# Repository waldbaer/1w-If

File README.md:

# 

An ESP32-based 1-Wire interface supporting access with physical ethernet and MQTT protocol.

**Overview**

**Hardware**

[Schematic](doc/hardware/1w-If_schematic.pdf)

## Key Features

* Access 1-wire devices via ethernet / MQTT protocol
* 4 independent 1-Wire channels with hardware bus masters
* Over-the-air (OTA) updates (web interface and espota protocol)
* Responsive web interface for configuration
  <br/>
  
* NTP for clock synchronization
* 3D printed housing

## Supported 1-Wire devices

* DS2401 / DS2411 (Silicon Serial Number)
  * Unique Unique 64-Bit Serial Code

* DS18B20 (Temperature sensor)
  * Configurable resolution temperature

* DS2438  (Smart Battery Monitor)
  * Temperature, VAD, VDD

## Web-Interface

Default login:
- Username: `admin`
- Password: `1w-If`

## MQTT API
`%topic%` is a configurable prefix. Default: `1wIf`

### Commands

General MQTT topic for commands: `%topic%/cmd`

General MQTT topic for responses and status: `%topic%/stat`

Payload Format:

```
{
  "action": "<command>",
  ... action specific parameters / attributes ...
}
```

#### Command 'Restart'

Restart the entire system.
```
{
  "action": "restart",
}
```

Response:
```
{
  "action": "restart",
  "acknowledge": true,
  "time": "2026-02-03 20:20:07.955"
}
```

#### Command 'SysInfo'

Get system info.
```
{
  "action": "sysinfo",
}
```

Response:
```
{
  "action": "sysinfo",
  "state": "online",
  "version": "1.1.0",
  "uptime": "14d 12:07:12.834",
  "board_temp": 43.9,
  "ethernet": {
    "ip": "192.168.0.100",
    "mac": "89:30:5A:47:7D:0C",
    "link_speed": 100,
    "link_mode": "FULL_DUPLEX"
  },
  "time": "2026-03-15 17:02:09.720"
}
```

#### Command 'Scan'

Scan 1-wire buses for all available devices:

```
{
  "action": "scan",
}
```

Scan 1-wire buses for availability of a specific device:

```
{
  "action": "scan",
  "device_id": "01.D2C79A1A0000"
}
```

Scan 1-wire buses for availability of a specific device family:

```
{
  "action": "scan",
  "family_code": 40
}
```

The response lists all available devices and the supported attributes (for `Read` / `Subscribe` / `Unsubscribe` commands):

Example Response:
```
{
  "action": "scan",
  "devices": [
    {
      "channel": 1,
      "device_id": "01.D2C79A1A0000",
      "presence": true,
      "attributes": ["presence"]
    },
    {
      "channel": 1,
      "device_id": "28.8F0945161301",
      "presence": true,
      "attributes": ["presence", "temperature"]
    },
    {
      "channel": 2,
      "device_id": "26.563743020000",
      "presence": true,
      "attributes": ["presence", "temperature", "VAD", "VDD"]
    },
    ...
  ],
  "time": "2026-02-03 20:16:46.010"
}
```

#### Command 'Read'

Read value(s) of a single 1-wire device:

```
{
  "action": "read",
  "device_id": "28.8F0945161301",
  "attribute": "temperature"
}
```

Example Response:
```
{
  "action": "read",
  "device": {
    "channel": 1,
    "device_id": "28.8F0945161301",
    "temperature": 24.75
  },
  "time": "2025-02-03 19:10:07.955"
}
```

Read value(s) of a specific device family:

```
{
  "action": "read",
  "family_code": 40,
  "attribute": "temperature"
}
```

Example Response:
```
{
  "action": "read",
  "family_code": 40,
  "devices": [
    {
      "channel": 1,
      "device_id": "28.8F0945161301",
      "temperature": 24.75
    },
    ...
  ],
  "time": "2025-02-03 18:10:02.844"
}
```

Also the presence of a device can be accessed via the read command using the attribute `presence`.
This is similar to the scan command.

```
{
  "action": "read",
  "device_id": "28.8F0945161301",
  "attribute": "presence"
}
```

Example Response:
```
{
  "action": "read",
  "device": {
    "channel": 2,
    "device_id": "28.8F0945161301",
    "presence": true
  },
  "time": "2026-01-17 05:19:02.170"
}
```

#### Command 'Subscribe / Unsubscribe'

Subscribe to cyclic updates for 1-wire device attributes.
After successful subscription this triggers internally a `Read` command with the configured internal time.

Unit of 'interval': _milliseconds_

```
{
  "action": "subscribe",
  "device_id": "28.8F0945161301",
  "attribute": "temperature",
  "interval": 1000
}
```

Example response acknowledging the successful subscription:
```
{
  "action": "subscribe",
  "acknowledge": true,
  "device": {
    "device_id": "28.8F0945161301"
  },
  "time": "2025-08-05 13:10:22.970"
}
```

Unsubscribe from the attribute:
```
{
  "action": "unsubscribe",
  "device_id": "28.8F0945161301",
  "attribute": "temperature"
}
```

It is also possible to subscribe to the attribute `presence` to get cyclic updates about the availability of dedicated
devices:
```
{
    "action": "subscribe",
    "device_id": "01.D2C79A1A0000",
    "attribute": "presence",
    "interval": 2000
}
```

Example of the `Read` command for attribute `presence` cyclically triggered by the subscription:
```
{
  "action": "read",
  "device": {
     "channel": 3,
     "device_id": "01.D2C79A1A0000",
     "presence": false
  },
  "time": "2026-01-20 14:55:36.781"
}
```

### Last Will and Testament

The MQTT Last Will and Testament (LWT) message is published to the `%topic%/stat` topic.

The LWT contains the attribute `state` with the value `offline`.
It also includes the timestamp of when the LWT was registered with the MQTT broker.

Example:
```
{
  "state": "offline",
  "time": "2026-02-27 21:52:59.016"
}
```

During startup and registration with the MQTT broker, the same message is published with `state` set to `online`.
In this case, the timestamp contains the time of the initial MQTT subscription performed by the 1-Wire interface.

Example:
```
{
  "state": "online",
  "time": "2026-02-27 22:04:17.125"
}
```

## Development

### Firmware
```
cd firmware

# Build firmware
./build.sh

# Flash firmware + LittleFS filesystem
./flash.sh
./flash-fs.sh

# Optional: Monitor via websocket
./monitor.sh
```

Run tests
```
cd test
pdm install --dev

# Create a test_env_config.yaml in the test directory
cp example_test_env_config.yaml test_env_config.yaml
# Adapt all MQTT / device settings test_env_config.yaml
vim test_env_config.yaml

# Execute tests
pdm run tests
# Alternative: with filter
pdm run tests -k "<test name filter>"

# Lint/Format of test implementations
pdm run lint
pdm run format
```

### Hardware

- PCB designed with [KiCad](https://www.kicad.org/)
- Production files created with KiCad plugin [KiCAD JLCPCB tools](https://github.com/Bouni/kicad-jlcpcb-tools)
- Housing designed with [onshape.com](https://www.onshape.com/)

#### 3D Printing Settings

* Bottom / Top Parts:
  * Material: PLA / HPA
  * 0.4mm nozzle
  * Perimeters: 2
  * Infill:
    * General: 15%
    * Screw Domes: 100% concentric
* DIN Rail Clip:
  * Material: PETG
  * 0.4mm nozzle
  * Perimeters: 2
  * Infill:
    * General: 15%
    * Screw Domes: 100% concentric

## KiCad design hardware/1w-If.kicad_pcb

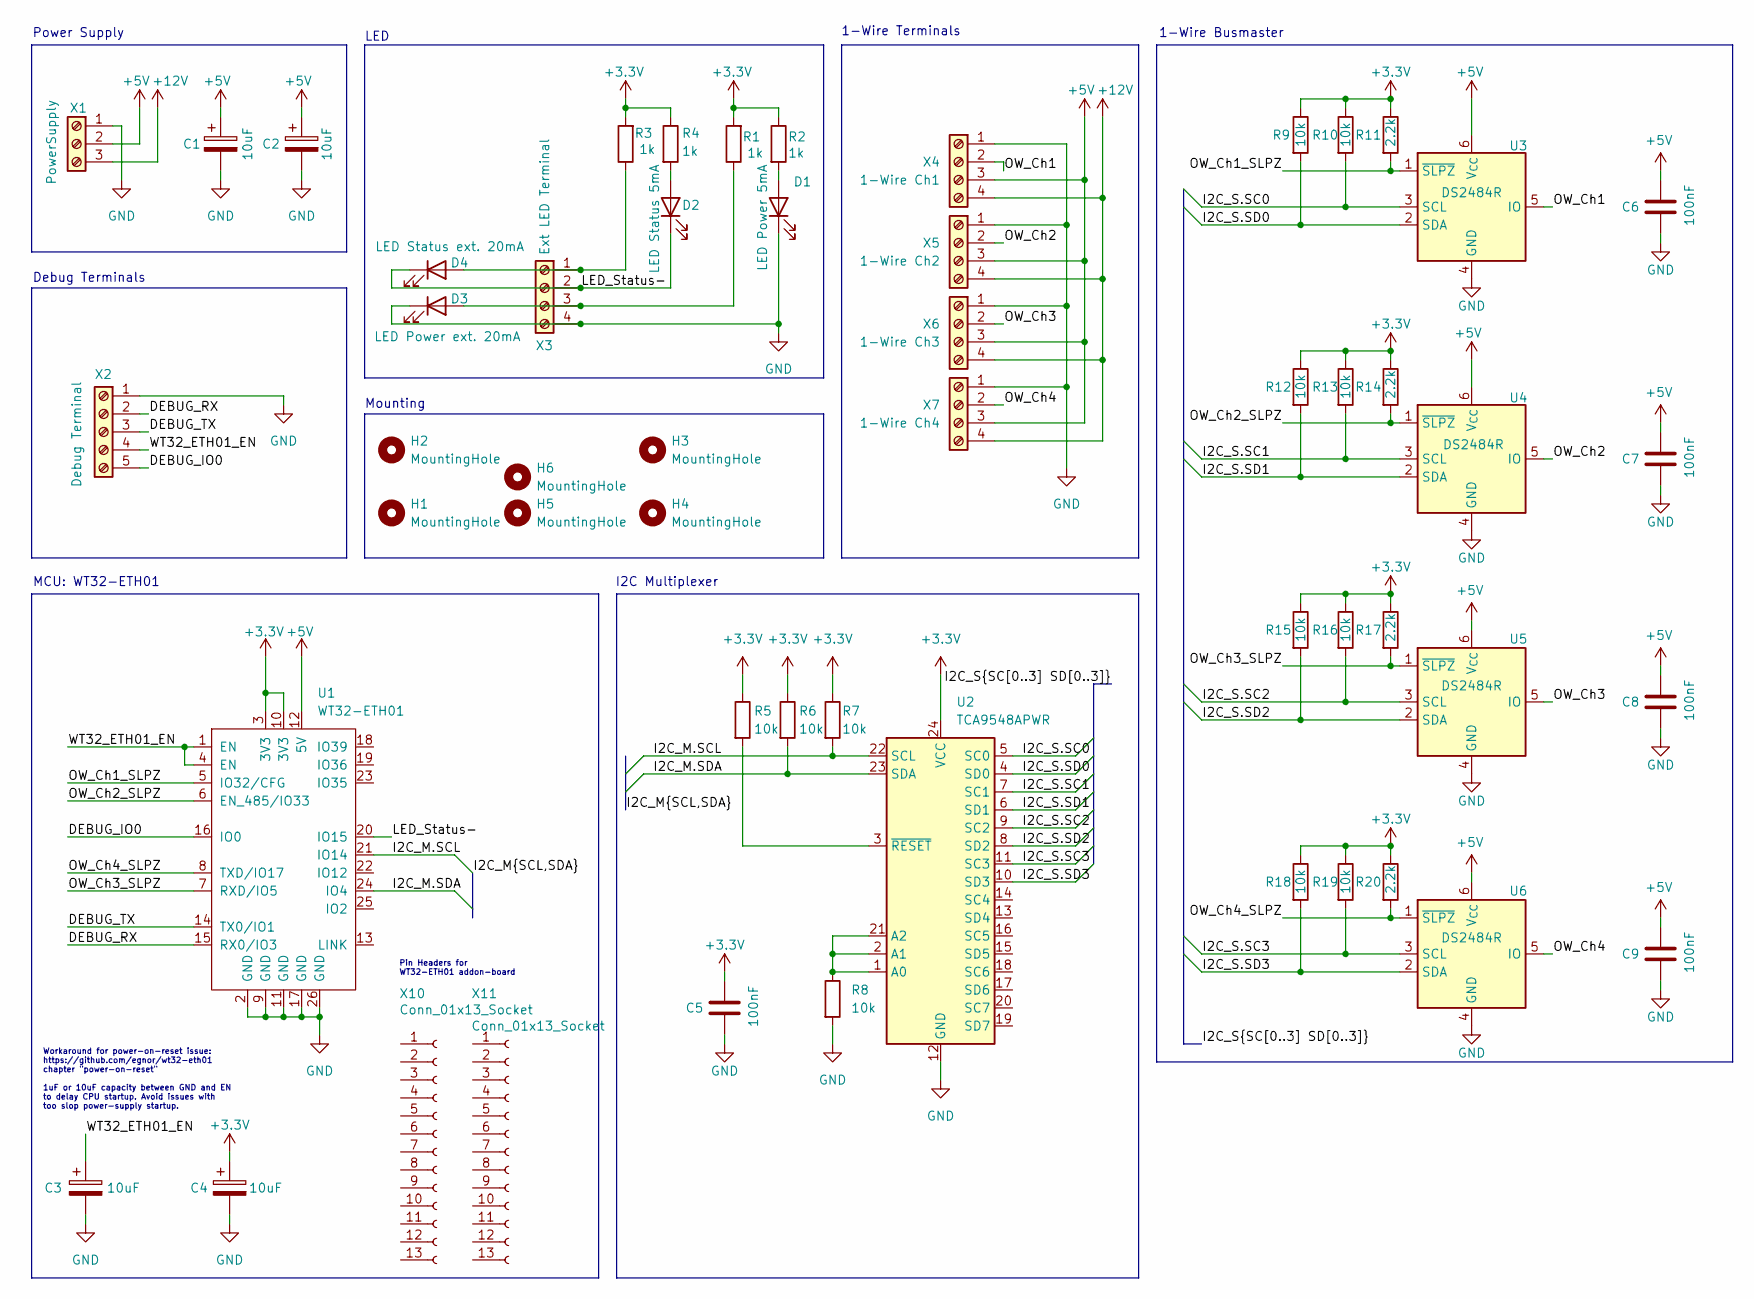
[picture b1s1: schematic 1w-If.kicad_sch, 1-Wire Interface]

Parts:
C1, C3, C4: 10uF; CP_EIA-3216-18_Kemet-A_HandSolder; LCSC C7171
C2: 10uF; CP_EIA-3216-18_Kemet-A_HandSolder
C5, C6, C7, C8, C9: 100nF; C_0805_2012Metric_Pad1.18x1.45mm_HandSolder; LCSC C49678
D1: LED Power 5mA; LED_0805_2012Metric_Pad1.15x1.40mm_HandSolder; LCSC C2297
D2: LED Status 5mA; LED_0805_2012Metric_Pad1.15x1.40mm_HandSolder; LCSC C34499
D3: LED Power ext. 20mA; LED_0805_2012Metric_Pad1.15x1.40mm_HandSolder; LCSC C2297
D4: LED Status ext. 20mA; LED_0805_2012Metric_Pad1.15x1.40mm_HandSolder; LCSC C2297
H1, H2, H3, H4, H5, H6: MountingHole; MountingHole_3.2mm_M3_DIN965
R1, R2, R3, R4: 1k; R_0805_2012Metric_Pad1.20x1.40mm_HandSolder; LCSC C17408
R5, R6, R7, R8, R9, R10, R12, R13, R15, R16, R18, R19: 10k; R_0805_2012Metric_Pad1.20x1.40mm_HandSolder; LCSC C17414
R11, R14, R17, R20: 2.2k; R_0805_2012Metric_Pad1.20x1.40mm_HandSolder; LCSC C17520
U1: WT32-ETH01; WT32-ETH01_inv_mount
U2: TCA9548APWR; TSSOP-24_4.4x7.8mm_P0.65mm; LCSC C130026
U3, U4, U5, U6: DS2484R; SOT-23-6; LCSC C124886
X1: PowerSupply; TerminalBlock_WAGO_2601-1103_1x03_P3.50mm_Horizontal
X2: Debug Terminal; TerminalBlock_WAGO_2601-1105_1x05_P3.50mm_Horizontal
X3: Ext LED Terminal; TerminalBlock_MetzConnect_Type086_RT03404HBLC_1x04_P3.81mm_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
X4: 1-Wire Ch1; TerminalBlock_WAGO_2601-1104_1x04_P3.50mm_Horizontal
X5: 1-Wire Ch2; TerminalBlock_WAGO_2601-1104_1x04_P3.50mm_Horizontal
X6: 1-Wire Ch3; TerminalBlock_WAGO_2601-1104_1x04_P3.50mm_Horizontal
X7: 1-Wire Ch4; TerminalBlock_WAGO_2601-1104_1x04_P3.50mm_Horizontal
X10, X11: Conn_01x13_Socket

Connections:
+3.3V: C4.1, C5.1, R1.2, R2.1, R3.2, R4.1, R5.1, R6.1, R7.1, R9.1, R10.1, R11.1, R12.1, R13.1, R14.1, R15.1, R16.1, R17.1, R18.1, R19.1, R20.1, U1.3 (3V3), U1.10 (3V3), U2.24 (VCC)
+5V: C1.1, C2.1, C6.1, C7.1, C8.1, C9.1, U1.12 (5V), U3.6 (V_{CC}), U4.6 (V_{CC}), U5.6 (V_{CC}), U6.6 (V_{CC}), X1.2, X4.3, X5.3, X6.3, X7.3
+12V: X1.3, X4.4, X5.4, X6.4, X7.4
/DEBUG_IO0: U1.16 (IO0), X2.5
/DEBUG_RX: U1.15 (RX0/IO3), X2.2
/DEBUG_TX: U1.14 (TX0/IO1), X2.3
/I2C_M.SCL: R7.2, U1.21 (IO14), U2.22 (SCL)
/I2C_M.SDA: R6.2, U1.24 (IO4), U2.23 (SDA)
/I2C_S.SC0: R10.2, U2.5 (SC0), U3.3 (SCL)
/I2C_S.SC1: R13.2, U2.7 (SC1), U4.3 (SCL)
/I2C_S.SC2: R16.2, U2.9 (SC2), U5.3 (SCL)
/I2C_S.SC3: R19.2, U2.11 (SC3), U6.3 (SCL)
/I2C_S.SD0: R9.2, U2.4 (SD0), U3.2 (SDA)
/I2C_S.SD1: R12.2, U2.6 (SD1), U4.2 (SDA)
/I2C_S.SD2: R15.2, U2.8 (SD2), U5.2 (SDA)
/I2C_S.SD3: R18.2, U2.10 (SD3), U6.2 (SDA)
/LED_Status-: D2.1 (K), D4.1 (K), U1.20 (IO15), X3.2
/OW_Ch1: U3.5 (IO), X4.2
/OW_Ch1_SLPZ: R11.2, U1.5 (IO32/CFG), U3.1 (~SLPZ)
/OW_Ch2: U4.5 (IO), X5.2
/OW_Ch2_SLPZ: R14.2, U1.6 (EN_485/IO33), U4.1 (~SLPZ)
/OW_Ch3: U5.5 (IO), X6.2
/OW_Ch3_SLPZ: R17.2, U1.7 (RXD/IO5), U5.1 (~SLPZ)
/OW_Ch4: U6.5 (IO), X7.2
/OW_Ch4_SLPZ: R20.2, U1.8 (TXD/IO17), U6.1 (~SLPZ)
/WT32_ETH01_EN: C3.1, U1.1 (EN), U1.4 (EN), X2.4
GND: C1.2, C2.2, C3.2, C4.2, C5.2, C6.2, C7.2, C8.2, C9.2, D1.1 (K), D3.1 (K), R8.2, U1.2 (GND), U1.9 (GND), U1.11 (GND), U1.17 (GND), U1.26 (GND), U2.12 (GND), U3.4 (GND), U4.4 (GND), U5.4 (GND), U6.4 (GND), X1.1, X2.1, X3.4, X4.1, X5.1, X6.1, X7.1
unnamed: D1.2 (A), R2.2
unnamed: D2.2 (A), R4.2
unnamed: R8.1, U2.1 (A0), U2.2 (A1), U2.21 (A2)
unnamed: R5.2, U2.3 (~RESET)
unnamed: D4.2 (A), R3.1, X3.1
unnamed: D3.2 (A), R1.1, X3.3

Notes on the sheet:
1-Wire Busmaster
MCU: WT32-ETH01
Pin Headers for WT32-ETH01 addon-board
1-Wire Terminals
I2C Multiplexer
LED
Debug Terminals
Mounting
Workaround for power-on-reset issue: https://github.com/egnor/wt32-eth01 chapter "power-on-reset" 1uF or 10uF capacity between GND and EN to delay CPU startup. Avoid issues with too slop power-supply startup.
Power Supply

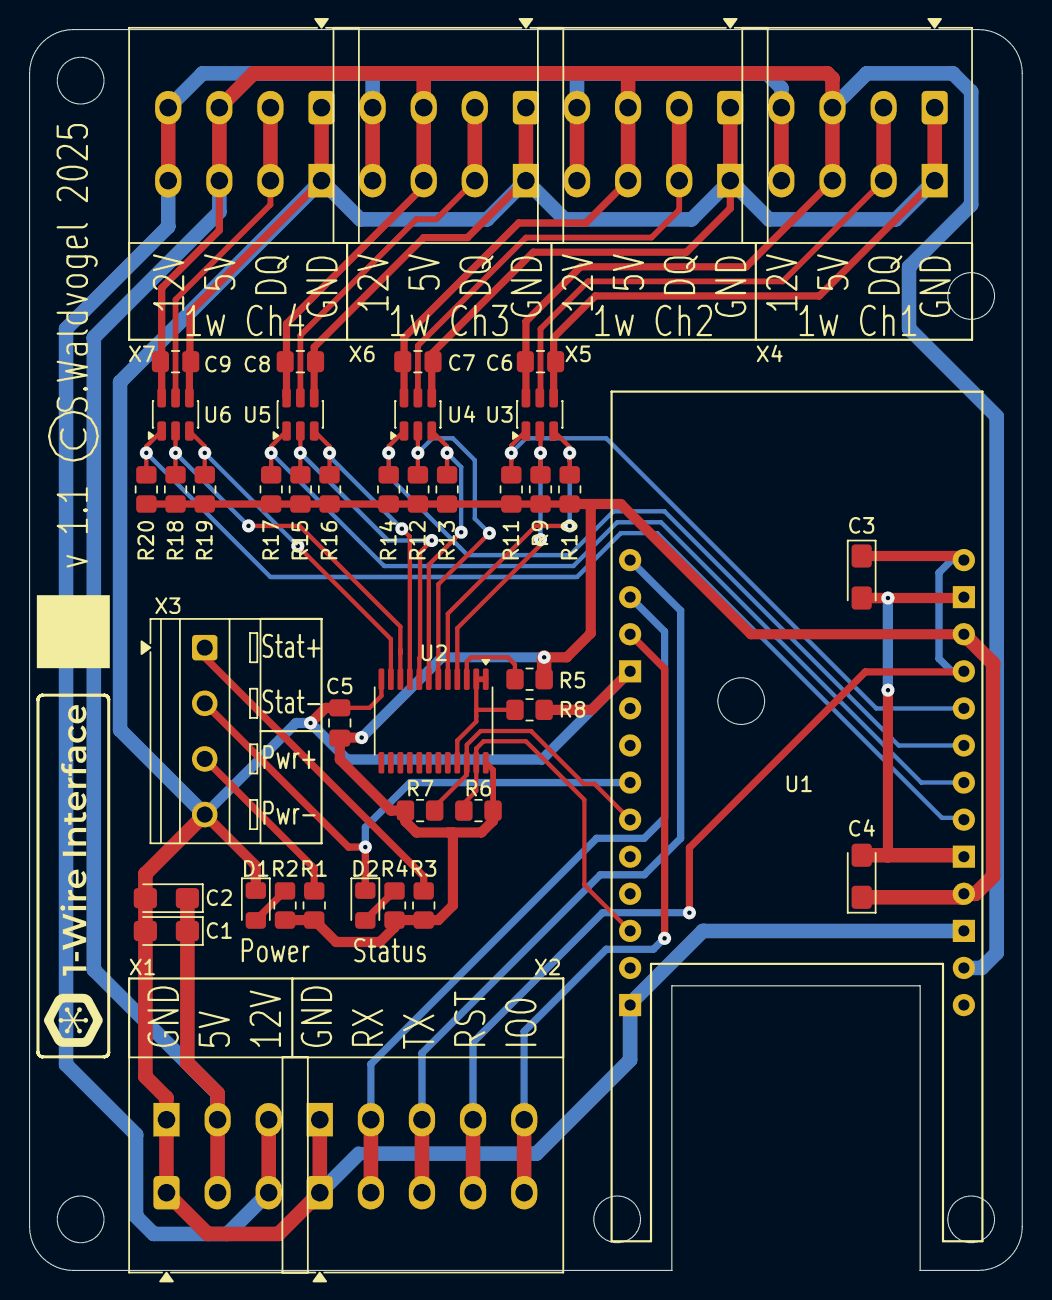
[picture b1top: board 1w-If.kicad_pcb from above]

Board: 2 copper layers, 68.0 x 85.0 mm, 50 parts (0 on the bottom side), 33 nets.

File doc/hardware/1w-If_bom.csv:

"Reference","Value","Datasheet","Footprint","Qty","DNP"
"C1,C2,C3,C4","10uF","https://www.lcsc.com/product-detail/C7171.html?href=jlc-SMT%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","Capacitor_Tantalum_SMD:CP_EIA-3216-18_Kemet-A_HandSolder","4",""
"C5,C6,C7,C8,C9","100nF","https://www.lcsc.com/product-detail/C49678.html?href=jlc-SMT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","Capacitor_SMD:C_0805_2012Metric_Pad1.18x1.45mm_HandSolder","5",""
"D1","LED Power 5mA","https://www.lcsc.com/product-detail/C2297.html?href=jlc-SMT%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","LED_SMD:LED_0805_2012Metric_Pad1.15x1.40mm_HandSolder","1",""
"D2","LED Status 5mA","https://www.lcsc.com/product-detail/C2297.html?href=jlc-SMT%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","LED_SMD:LED_0805_2012Metric_Pad1.15x1.40mm_HandSolder","1",""
"D3","LED Power ext. 20mA","https://www.reichelt.de/de/de/shop/suche/3034W2D-EHD-A?GROUP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","LED_SMD:LED_0805_2012Metric_Pad1.15x1.40mm_HandSolder","1",""
"D4","LED Status ext. 20mA","https://www.reichelt.de/de/de/shop/suche/3034W2D-EHD-A?GROUP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","LED_SMD:LED_0805_2012Metric_Pad1.15x1.40mm_HandSolder","1",""
"R1,R2,R3,R4","1k","https://www.lcsc.com/product-detail/C17408.html?href=jlc-SMT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","Resistor_SMD:R_0805_2012Metric_Pad1.20x1.40mm_HandSolder","4",""
"R5,R6,R7,R8,R9,R10,R12,R13,R15,R16,R18,R19","10k","https://www.lcsc.com/product-detail/C17414.html?href=jlc-SMT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","Resistor_SMD:R_0805_2012Metric_Pad1.20x1.40mm_HandSolder","12",""
"R11,R14,R17,R20","2.2k","https://www.lcsc.com/product-detail/C17520.html?href=jlc-SMT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","Resistor_SMD:R_0805_2012Metric_Pad1.20x1.40mm_HandSolder","4",""
"U1","WT32-ETH01","http://www.wireless-tag.com/wp-content/uploads/2020/08/WT32-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","WT32-ETH01:WT32-ETH01_inv_mount","1",""
"U2","TCA9548APWR","http://www.ti.com/lit/ds/symlink/tca9548a.pdf","Package_SO:TSSOP-24_4.4x7.8mm_P0.65mm","1",""
"U3,U4,U5,U6","DS2484R","https://www.analog.com/DS2484/datasheet","Package_TO_SOT_SMD:SOT-23-6","4",""
"X1","PowerSupply","https://www.reichelt.de/de/de/shop/produkt/leiterplattenklem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","TerminalBlock_WAGO_3D:TerminalBlock_WAGO_2601-1103_1x03_P3.50mm_Horizontal","1",""
"X2","Debug Terminal","https://www.reichelt.de/de/de/shop/produkt/leiterplattenklem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","TerminalBlock_WAGO_3D:TerminalBlock_WAGO_2601-1105_1x05_P3.50mm_Horizontal","1",""
"X3","Ext LED Terminal","https://www.reichelt.de/de/de/shop/produkt/anschlussklemme_4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","TerminalBlock_MetzConnect_3D:TerminalBlock_MetzConnect_Type086_RT03404HBLC_1x04_P3.81mm_Horizontal","1",""
"X4","1-Wire Ch1","https://www.reichelt.de/de/de/shop/produkt/leiterplattenklem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","TerminalBlock_WAGO_3D:TerminalBlock_WAGO_2601-1104_1x04_P3.50mm_Horizontal","1",""
"X5","1-Wire Ch2","https://www.reichelt.de/de/de/shop/produkt/leiterplattenklem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","TerminalBlock_WAGO_3D:TerminalBlock_WAGO_2601-1104_1x04_P3.50mm_Horizontal","1",""
"X6","1-Wire Ch3","https://www.reichelt.de/de/de/shop/produkt/leiterplattenklem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","TerminalBlock_WAGO_3D:TerminalBlock_WAGO_2601-1104_1x04_P3.50mm_Horizontal","1",""
"X7","1-Wire Ch4","https://www.reichelt.de/de/de/shop/produkt/leiterplattenklem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","TerminalBlock_WAGO_3D:TerminalBlock_WAGO_2601-1104_1x04_P3.50mm_Horizontal","1",""
"X10,X11","Conn_01x13_Socket","https://www.reichelt.de/de/de/shop/produkt/buchsenleiste_2_5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","","2",""

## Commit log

2025-09-28 1w-If: Initial version
2025-09-28 Updated overview
2025-09-30 Move crc8 to util namespace
2025-10-03 Improve OneWireAddress, Timer and string logging
2025-10-05 Cleanup command handlers
2025-10-05 Improve abort / terminate handling
2025-10-05 Support command 'restart'
2025-10-05 github action: platform.io build
2025-10-05 re-format
2025-10-05 github action: platform.io build (#1)
    * github action: platform.io build
    * re-format
2025-10-05 Introduce PresenceCommandHandler
2025-10-05 Fix single device search
2025-10-05 Support attribute 'presence' for all device families
2025-10-14 Add support for espota uploads
2025-10-14 Support OTA config via web interface
2025-10-14 Refactor constants / defaults in persistency
2025-10-14 Add support for espota OTA updates (#2)
2025-10-27 Support web logger (using websocket)
2025-10-27 Support configuration of logging
2025-10-27 Support web logger (based on websocket) (#3)
2025-10-27 Fix: Missing device for action scan all
2025-10-29 [WebServer] Improve session handling
2025-10-29 [WebServer] Improve login & constants
2025-10-29 [WebServer] ResponseCode
2025-11-02 [WebServer] Move config to separate page
2025-11-02 [WebServer] Show available 1-wire devices on dashboard
2025-11-02 [WebServer] Rework title / menu bar
2025-11-02 Show 1-wire devices on dashboard (#4)
2025-11-02 Fix JsonBuilder deprecated API usage
2025-11-04 Responsive web UI
2025-11-04 Mark current menu element active
2025-11-04 Responsive web UI (#5)
2025-11-04 Added web UI screenshots
2025-11-04 Add web UI smaller screenshot
2025-11-05 CSS finetuning
2025-11-06 Show actual devices instead of test devicelist
2025-11-06 show actual devices instead of test data
2025-11-06 [WebServer] 30min session timeout
2025-11-08 [WebServer] Add favicon
2025-11-09 Testsuite for MQTT protocol
2025-11-09 Testsuite for MQTT protocol (#6)
2025-11-15 Added more logo details
2025-11-15 [WebServer] Use password placeholder in UI
2025-11-15 [WebServer] fix javascript error in console
2025-11-16 [Logging] Fix broken logs during startup
2025-11-16 [WebServer] fix partial config update of passwords
2025-11-16 [WebSocketLogger] Fix too many queued messages
2025-11-16 Show 1-wire channel in device overview
2025-11-16 Add 1-wire channel to MQTT protocol
2025-11-16 Add one-wire channel to MQTT protocol and web UI overview (#7)
2025-11-19 Vectorize logo
2025-11-26 More logo vectorization
    * Vectorize logo font
    * Add logo font 'Montserrat' to repo
    * Add logo variant 'logo-white-transparent-framed'
2025-11-26 WebServer: Use svg logo variant
2025-12-02 Hardware PCB for 1w-If (v1.0)
2025-12-02 Hardware PCB for 1w-If (v1.0) (#8)
2025-12-06 Improve 3D model of WT32-ETH01
2025-12-06 Add more PCB parts
2025-12-07 C1-C4: Fix polarity | R1+R3: Adapt for 20mA external LEDs
2025-12-07 Overview as SVG
2025-12-14 - Too bright LEDs: R1-R4 changed to 1kOhm - Swapped ext. LED connector silk layer description
2025-12-14 PCB v1.1 (#9)
    - Add missing polarity of tantal capacities C1-C4.
    - Too bright LEDs: R1-R4 changed to 1kOhm
    - Swapped ext. LED connector silk layer description
2025-12-14 Increase test robustness
2025-12-14 Support 4 1-wire channels and status LED
2025-12-14 Support 4 independent 1-wire channels (#10)
    - Support 4 1-wire channels and status LED
2025-12-15 Improve readability of overview
2025-12-15 Add PCB pictures
2025-12-15 Improve PCV pictures
2025-12-15 Improve flash/monitor scripts
2025-12-16 Introduce LedStatus abstraction
2025-12-16 Visualize OTA flash process with the StatusLed
2025-12-19 Configurable 1-Wire channel activation
2025-12-19 Configurable 1-Wire channel activation (#11)
2025-12-19 PrettyPrint config
2025-12-19 PrettyPrint config (#12)
2025-12-19 Logging Config: Enable verbose log-level and serial sink by default
2025-12-20 Added pin connectors for WT32_ETH01 Reworked BOM / datasheets
2025-12-20 Fix schematic link
2025-12-28 Fix console separation of apps with whitespace
2025-12-28 Add empty attributes array if not attributes are supported
2025-12-28 Several web UI style fixes
2025-12-30 Sorted devices list and devices web UI improvements
2026-01-02 Support configurable MQTT client ID
2026-01-02 Support configurable MQTT client ID (#13)
2026-01-11 Show system info (version, uptime, eth info) on dashboard. Derive Version from git.
2026-01-11 Show system info (version, uptime, eth info) on dashboard. Derive Version from git. (#14)
2026-01-11 Improve compact_table styling
2026-01-11 Bump esp32async/ESPAsyncWebServer from 3.8.1 -> 3.9.4
2026-01-11 Bump esp32async/ESPAsyncWebServer from 3.8.1 -> 3.9.4 (#15)
2026-01-18 Rework logo: thicker star
2026-01-20 Properly format multi-day timestamps
2026-01-22 Move TimeUtil into separate namespace 'time'
2026-01-22 Support date/time synchronized from NTP server
2026-01-24 Support NTP config
2026-01-24 DateTime synchronized from NTP server (#16)
2026-01-25 Fix unknown git revision in esptool build env
2026-01-25 Bump ESPAsyncWebServer 3.9.4 -> 3.9.5
2026-01-25 GitHub Actions: Build also esptool env
2026-01-25 Fix pio command
2026-01-25 Bump ESPAsyncWebServer 3.9.4 -> 3.9.5 (#17)
2026-01-29 DIN Rail Enclosure
2026-01-29 DIN Rail Housing (3D Print) (#18)
2026-02-01 Show CPU temperature on dashboard
2026-02-03 Add current timestamp to JSON responses
2026-02-03 Add current timestamp to JSON responses (#19)
2026-02-03 Fix typo
2026-02-03 Move firmware into subfolder 'firmware'
2026-02-03 Move firmware into subfolder (#20)
2026-02-03 Improve monitor script
2026-02-06 [Housing] Add ventilation cuts
2026-02-06 Show configured hostname in website titles
2026-02-06 Flash status LED while command processing
2026-02-06 Update screenshots
2026-02-06 Prepare 1.0.0 release
2026-02-23 [Housing] Improve north/south WAGO cuts
2026-02-23 Cleanup .vscode / .gitignore
2026-02-27 [Housing] Update pictures
2026-02-27 [Housing] Update rendering
2026-02-27 Support Last Will and Testament (LWT)
2026-02-27 Support Last Will and Testament (LWT) (#21)
2026-02-27 Bump ESPAsyncWebServer from 3.9.5 to 3.10.0
2026-02-27 Bump ESPAsyncWebServer from 3.9.5 to 3.10.0 (#22)
2026-03-15 Bump ESPAsyncWebServer from 3.10.0 to 3.10.1
2026-03-15 Bump ESPAsyncWebServer from 3.10.0 to 3.10.1 (#23)
2026-03-15 Introduce action 'sysinfo'
2026-03-15 Introduce action 'sysinfo' (#24)
2026-03-15 Changelog for v1.1.0 release
2026-06-08 Bump platformio/esperif32 from 6.12.0 to 7.0.1
2026-06-08 Bump bblanchon/ArduinoJson from 7.4.2 to 7.4.3
2026-06-08 Bump bblanchon/ArduinoJson from 7.4.2 to 7.4.3 (#26)
2026-06-08 Bump platformio/espressif32 from 6.12.0 to 7.0.1
2026-06-08 Bump platformio/espressif32 from 6.12.0 to 7.0.1 (#27)
2026-06-08 Bump esp32async/ESPAsyncWebServer from 3.10.1 to 3.11.1
2026-06-08 Bump esp32async/ESPAsyncWebServer from 3.10.1 to 3.11.1 (#28)
